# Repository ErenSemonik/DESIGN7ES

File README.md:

# DESIGN7ES
The following project is a design publication for ENGN3055 - Engineering Design and Prototyping at Johnson & Wales University. This project is licensed under the MIT License. Please see the license file for details.

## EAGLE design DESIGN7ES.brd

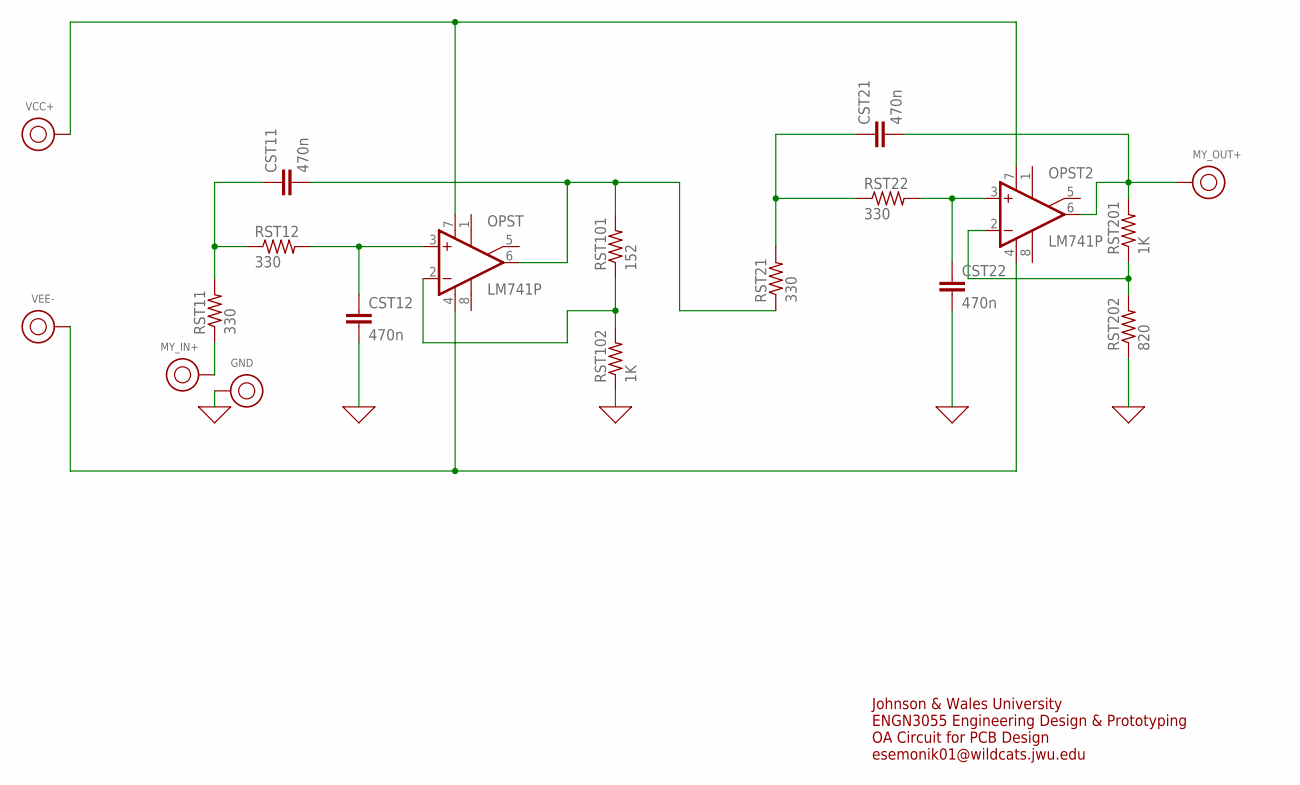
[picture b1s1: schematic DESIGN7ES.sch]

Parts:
CST11, CST12, CST21, CST22: 470n; C2.5-2
GND: BINDING-POST
MY_IN+: BINDING-POST
MY_OUT+: BINDING-POST
OPST, OPST2: LM741P; DIL08
RST11, RST12, RST21, RST22: 330; 0204/5
RST101: 152; 0204/5
RST102, RST201: 1K; 0204/5
RST202: 820; 0204/5
VCC+: BINDING-POST
VEE-: BINDING-POST

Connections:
0: CST12.2, CST22.2, GND.1, GND.1_1, GND.1_2, GND.1_3, GND.1_4, GND.1_5, GND.1_6, GND.1_7, GND.1_8, RST102.1, RST202.1
unnamed: CST11.1, RST11.2, RST12.1
unnamed: CST12.1, OPST.3 (+IN), RST12.2
unnamed: OPST.2 (-IN), RST101.1, RST102.2
unnamed: CST11.2, OPST.6 (OUT), RST21.1, RST101.2
unnamed: OPST2.2 (-IN), RST201.1, RST202.2
unnamed: CST21.1, RST21.2, RST22.1
unnamed: CST22.1, OPST2.3 (+IN), RST22.2
unnamed: CST21.2, MY_OUT+.1, MY_OUT+.1_1, MY_OUT+.1_2, MY_OUT+.1_3, MY_OUT+.1_4, MY_OUT+.1_5, MY_OUT+.1_6, MY_OUT+.1_7, MY_OUT+.1_8, OPST2.6 (OUT), RST201.2
unnamed: MY_IN+.1, MY_IN+.1_1, MY_IN+.1_2, MY_IN+.1_3, MY_IN+.1_4, MY_IN+.1_5, MY_IN+.1_6, MY_IN+.1_7, MY_IN+.1_8, RST11.1
unnamed: OPST.7 (V+), OPST2.7 (V+), VCC+.1, VCC+.1_1, VCC+.1_2, VCC+.1_3, VCC+.1_4, VCC+.1_5, VCC+.1_6, VCC+.1_7, VCC+.1_8
unnamed: OPST.4 (V-), OPST2.4 (V-), VEE-.1, VEE-.1_1, VEE-.1_2, VEE-.1_3, VEE-.1_4, VEE-.1_5, VEE-.1_6, VEE-.1_7, VEE-.1_8

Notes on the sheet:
Johnson & Wales University ENGN3055 Engineering Design & Prototyping OA Circuit for PCB Design esemonik01@wildcats.jwu.edu

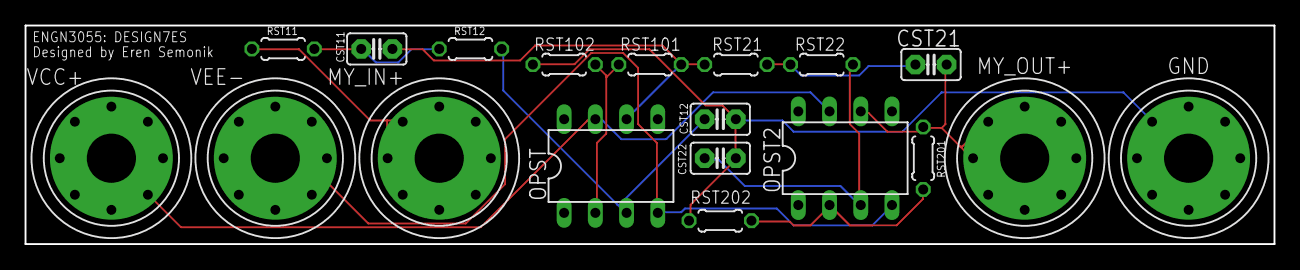
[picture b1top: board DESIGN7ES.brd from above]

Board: 2 copper layers, 101.6 x 17.8 mm, 19 parts (0 on the bottom side), 12 nets.
